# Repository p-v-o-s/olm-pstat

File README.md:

Potentiostat module for the Open Lab Monitor

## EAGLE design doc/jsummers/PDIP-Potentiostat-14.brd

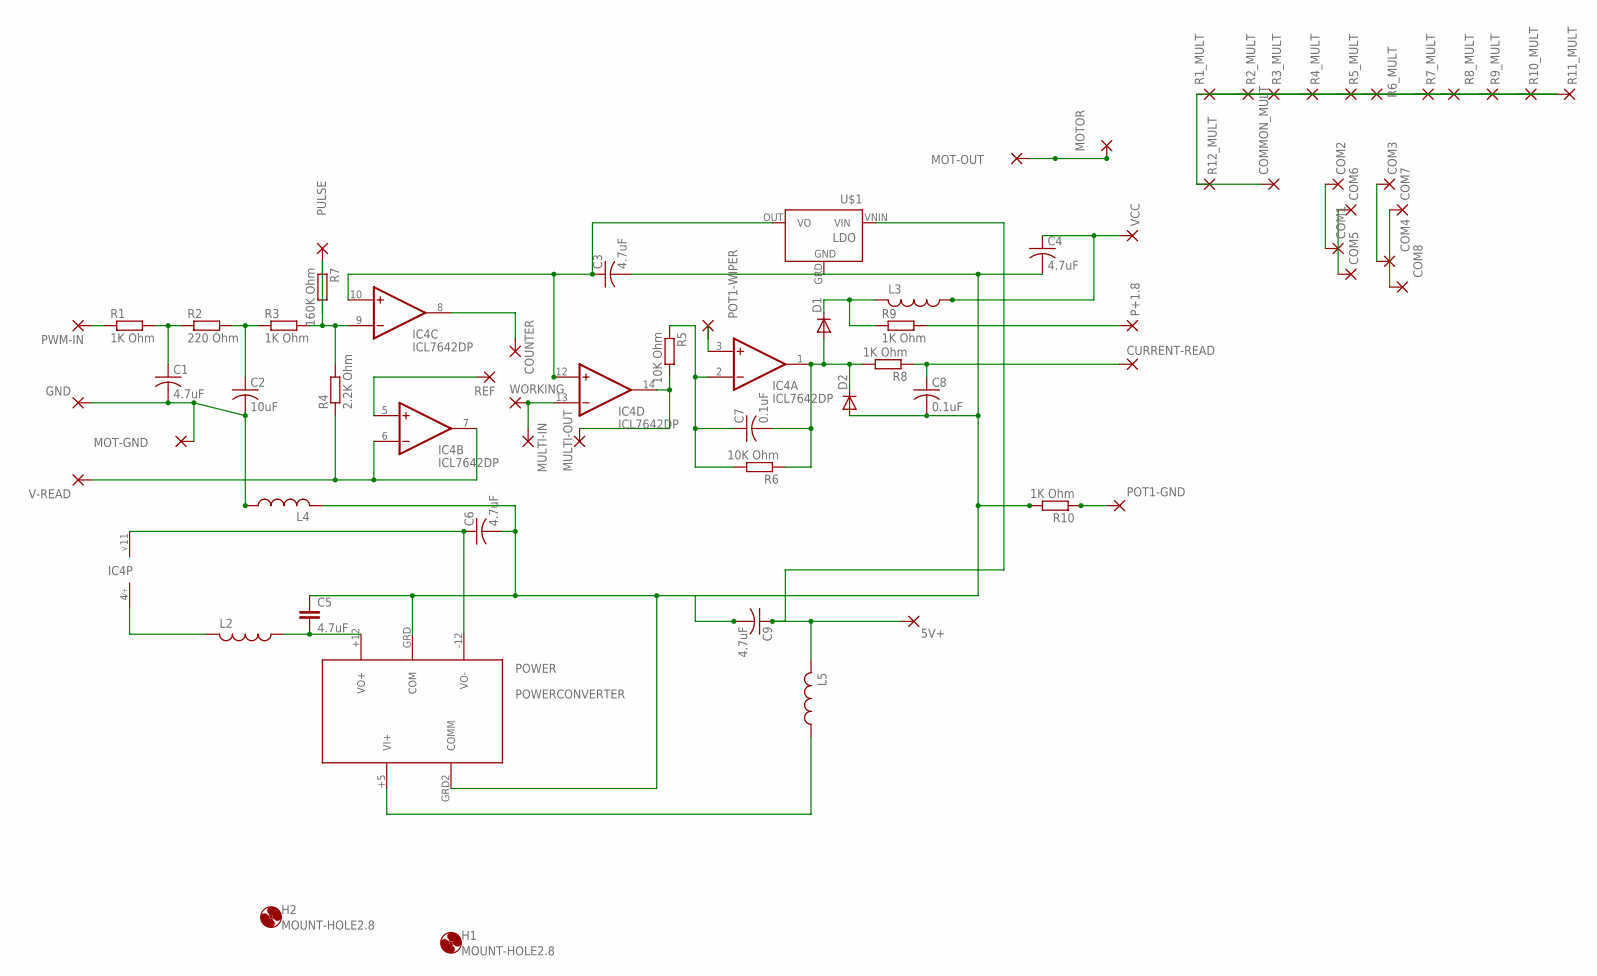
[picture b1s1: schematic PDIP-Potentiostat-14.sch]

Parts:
5V+: 1,6/0,9
C1, C3, C4, C5, C6, C9: 4.7uF; C025-050X050
C2: 10uF; C025-050X050
C7, C8: 0.1uF; C025-050X050
COM1, COM2, COM3, COM4, COM5, COM6, COM7, COM8: 1,6/0,9
COMMON_MULT: 1,6/0,9
COUNTER: 1,6/0,9
CURRENT-READ: 1,6/0,9
D1, D2: DIODE-D-7.5; D-7.5
GND: 1,6/0,9
H1, H2: MOUNT-HOLE2.8; 2,8
IC4: ICL7642DP; DIL14
L2, L3, L4, L5: L-USTFI0305; TFI0305
MOT-GND: 1,6/0,9
MOT-OUT: 1,6/0,9
MOTOR: 1,6/0,9
MULTI-IN: 1,6/0,9
MULTI-OUT: 1,6/0,9
P+1.8: 1,6/0,9
POT1-GND, POT1-WIPER: 1,6/0,9
POWER: POWERCONVERTER; HMM2
PULSE: 1,6/0,9
PWM-IN: 1,6/0,9
R1, R3, R8, R9, R10: 1K Ohm; 0204/7
R1_MULT, R2_MULT, R3_MULT, R4_MULT, R5_MULT, R6_MULT, R7_MULT, R8_MULT, R9_MULT, R10_MULT, R11_MULT, R12_MULT: 1,6/0,9
R2: 220 Ohm; 0204/7
R4: 2.2K Ohm; 0204/7
R5, R6: 10K Ohm; 0204/7
R7: 160K Ohm; 0204/7
REF: 1,6/0,9
U$1: LDO
V-READ: 1,6/0,9
VCC: 1,6/0,9
WORKING: 1,6/0,9

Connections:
+5V: D1.C, L3.2, R9.1
unnamed: L5.1, POWER.+5 (VI+)
unnamed: IC4.6 (-IN), IC4.7 (OUT), R4.1, V-READ.1
unnamed: IC4.5 (+IN), REF.1
unnamed: 5V+.1, C9.1, L5.2, U$1.VNIN (VIN)
unnamed: COUNTER.1, IC4.8 (OUT)
unnamed: IC4.14 (OUT), MULTI-OUT.1, R5.2
unnamed: C7.1, IC4.2 (-IN), R5.1, R6.2
unnamed: IC4.4 (V+), L2.2
unnamed: PWM-IN.1, R1.1
unnamed: IC4.9 (-IN), R3.2, R4.2, R7.2
unnamed: C3.2, C4.2, C5.1, C6.2, C8.2, C9.2, D2.A, L4.2, POWER.GRD (COM), POWER.GRD2 (COMM), R10.2, U$1.GRD (GND)
unnamed: PULSE.1, R7.1
unnamed: C1.1, R1.2, R2.1
unnamed: IC4.3 (+IN), POT1-WIPER.1
unnamed: C1.2, C2.2, GND.1, L4.1, MOT-GND.1
unnamed: C5.2, L2.1, POWER.+12 (VO+)
unnamed: IC4.13 (-IN), MULTI-IN.1, WORKING.1
unnamed: P+1.8.1, R9.2
unnamed: C2.1, R2.2, R3.1
unnamed: C7.2, D1.A, D2.C, IC4.1 (OUT), R6.1, R8.2
unnamed: COM3.1, COM4.1
unnamed: C3.1, IC4.10 (+IN), IC4.12 (+IN), U$1.OUT (VO)
unnamed: MOT-OUT.1, MOTOR.1
unnamed: C6.1, IC4.11 (V-), POWER.-12 (VO-)
unnamed: C8.1, CURRENT-READ.1, R8.1
unnamed: C4.1, L3.1, VCC.1
unnamed: POT1-GND.1, R10.1
unnamed: COM1.1, COM2.1
unnamed: COM7.1, COM8.1
unnamed: COM5.1, COM6.1
unnamed: COMMON_MULT.1, R1_MULT.1, R2_MULT.1, R3_MULT.1, R4_MULT.1, R5_MULT.1, R6_MULT.1, R7_MULT.1, R8_MULT.1, R9_MULT.1, R10_MULT.1, R11_MULT.1, R12_MULT.1

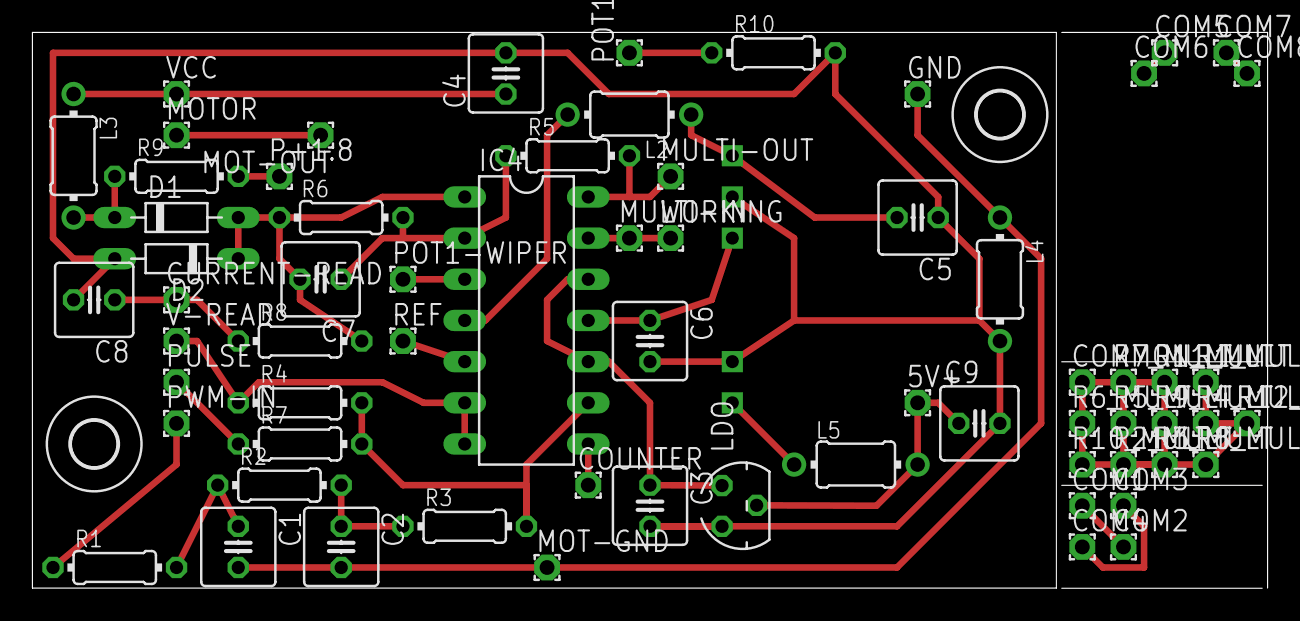
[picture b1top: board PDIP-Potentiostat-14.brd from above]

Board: 2 copper layers, 76.2 x 34.3 mm, 69 parts (0 on the bottom side), 32 nets.

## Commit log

2013-05-12 some data sheets; old PLOTS pstat source code (from Jack Summers)
2013-05-12 got rid of redundant file
2013-05-15 more part datasheets
2013-05-15 data set from test of Summers' Group DIY pstat
2013-05-15 fixed typo in plot title
2013-05-29 makefile for simple build tasks
2013-05-29 more docs and testing
2013-05-29 arduino firmware
2013-05-29 rename
2013-05-29 converted by Fritzing; custom part lost
2013-05-29 remove non-existent shutdown pin
2013-05-29 removed ~ files
2013-05-29 testing plot
2013-05-29 added class member for voltage reference
2013-06-18 testing DAC
2013-06-18 more datasheets
2013-08-09 DAC library functionality
2013-08-09 moved folder part 1
2013-08-09 moved folder part 2
2013-08-09 ADC library functionality
2013-08-09 Dig Pot library functionality
2013-08-09 Test code for ADC and Dig Pot
2013-08-10 main firmware file
2013-08-10 testing voltage control range
2013-08-13 added VCTRL command to set controlled voltage
2013-08-13 calibration of digital potentiometer
2013-08-13 Python code to plot voltage sweep test
2013-08-13 fixed data set names
2013-08-27 lots of added functionality and documentation
2013-09-01 implemented CMOS Analog MUX chip
2013-09-01 better voltage calibration; restored command functionality
2013-09-01 initialize and cache wiper settings
2013-09-01 read wiper settings
2013-09-01 removed junk ~ files
2013-09-01 removed junk
2013-09-02 python package layout
2013-09-02 moved code into package
2013-09-02 changed 'nested' commands to '.' separation
2013-09-02 added package setup file
2013-09-02 for dev tasks
2013-09-02 added open source liscence
2013-09-02 implemented current sensing range switching and autoranging functionality
2013-09-02 moved data to test folder
2013-09-02 moved into new scripts subpackage
2013-09-02 make into a subpackage
2013-09-02 fix chip type in comment
2013-09-02 basis for GUI control code
2013-09-02 created entry points for shell scripts; rename status update script
2013-09-02 created entry points for shell scripts
2013-09-02 added command line argument parsing
2013-09-02 push device driver back under subpackages
2013-09-02 have setup create the package configuration directory structure compatible with Automat
2013-09-02 created the shell application
2013-09-02 refactored into an Automat Device Interface
2013-09-02 added directory for configuration
2013-09-02 added example config
2013-09-02 added interface configurator for Automat compatibility
2013-09-02 refactored to use new automat.services.application.ShellApplication generic application foundation class
2013-09-02 comment tweaks
2013-09-02 refactored to use new automat.services.application.ApplicationBase generic application foundation class
2013-09-03 staging control as an app with GUI
2013-09-03 added crash handling decorator on main function
2013-09-03 core functionality for the framework; template for Current vs. Voltage plot
2013-09-03 trimmed trailing newline
2013-09-03 basic GUI husk for control app up and running
2013-09-05 added graphics
2013-09-06 lots of changes; real-time CV implemented
2013-09-06 echem test data
2013-11-24 added cleaning of .pyc files
2013-11-24 added ABORT serial command
2013-11-24 prepping for exportation of sweep data
2013-11-24 prepping for exportation of sweep data; updating plot boundaries when data exceeds limits
2013-11-24 allow for aborting of sweep
2013-11-24 allow for aborting of sweep; fix DEFAULT_EOL no defined bug
